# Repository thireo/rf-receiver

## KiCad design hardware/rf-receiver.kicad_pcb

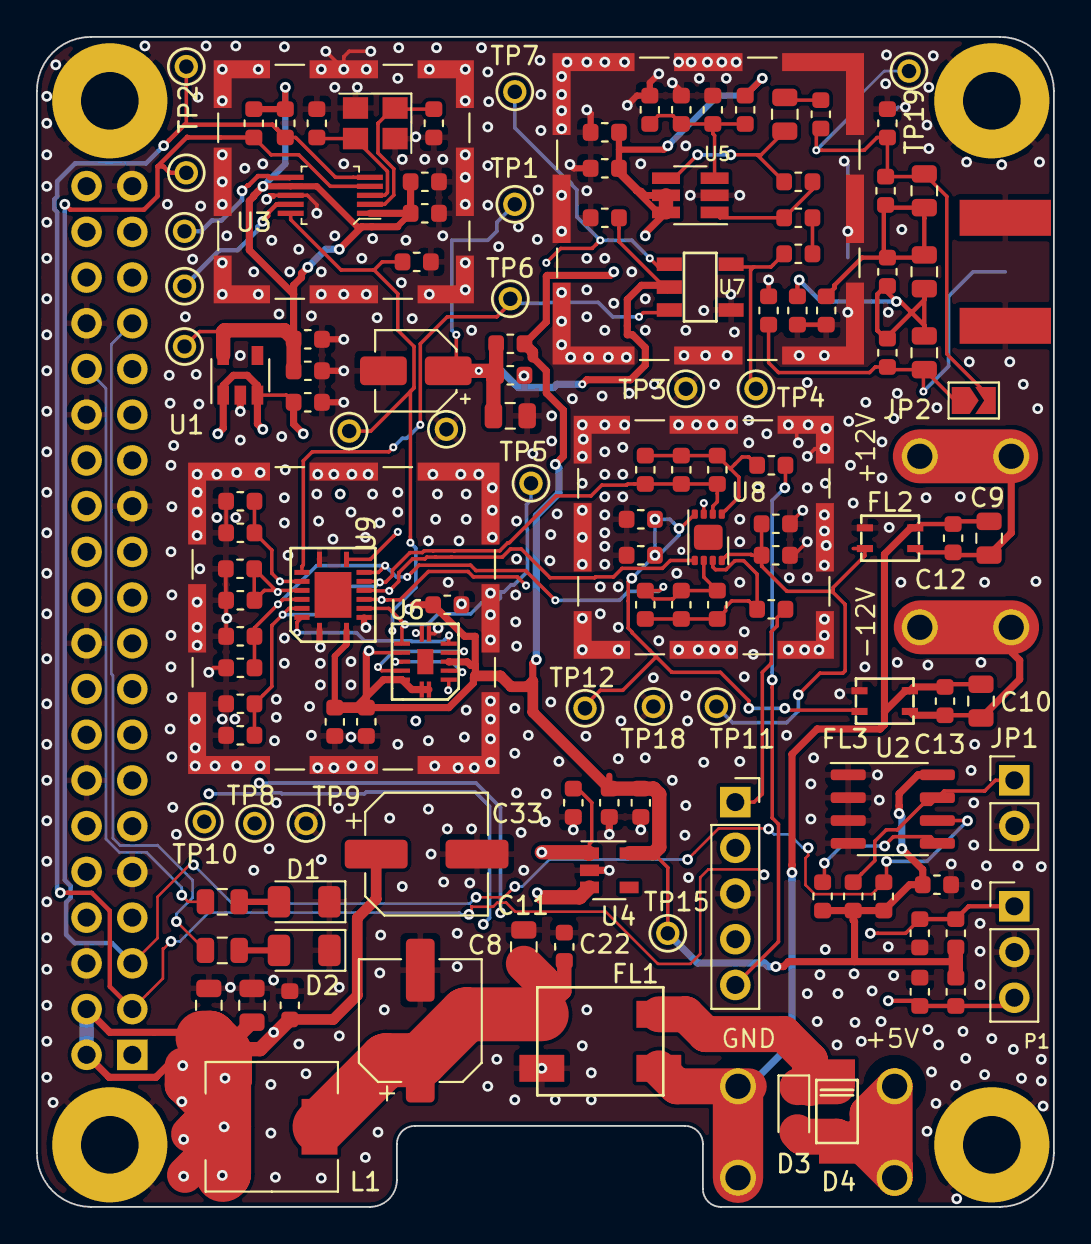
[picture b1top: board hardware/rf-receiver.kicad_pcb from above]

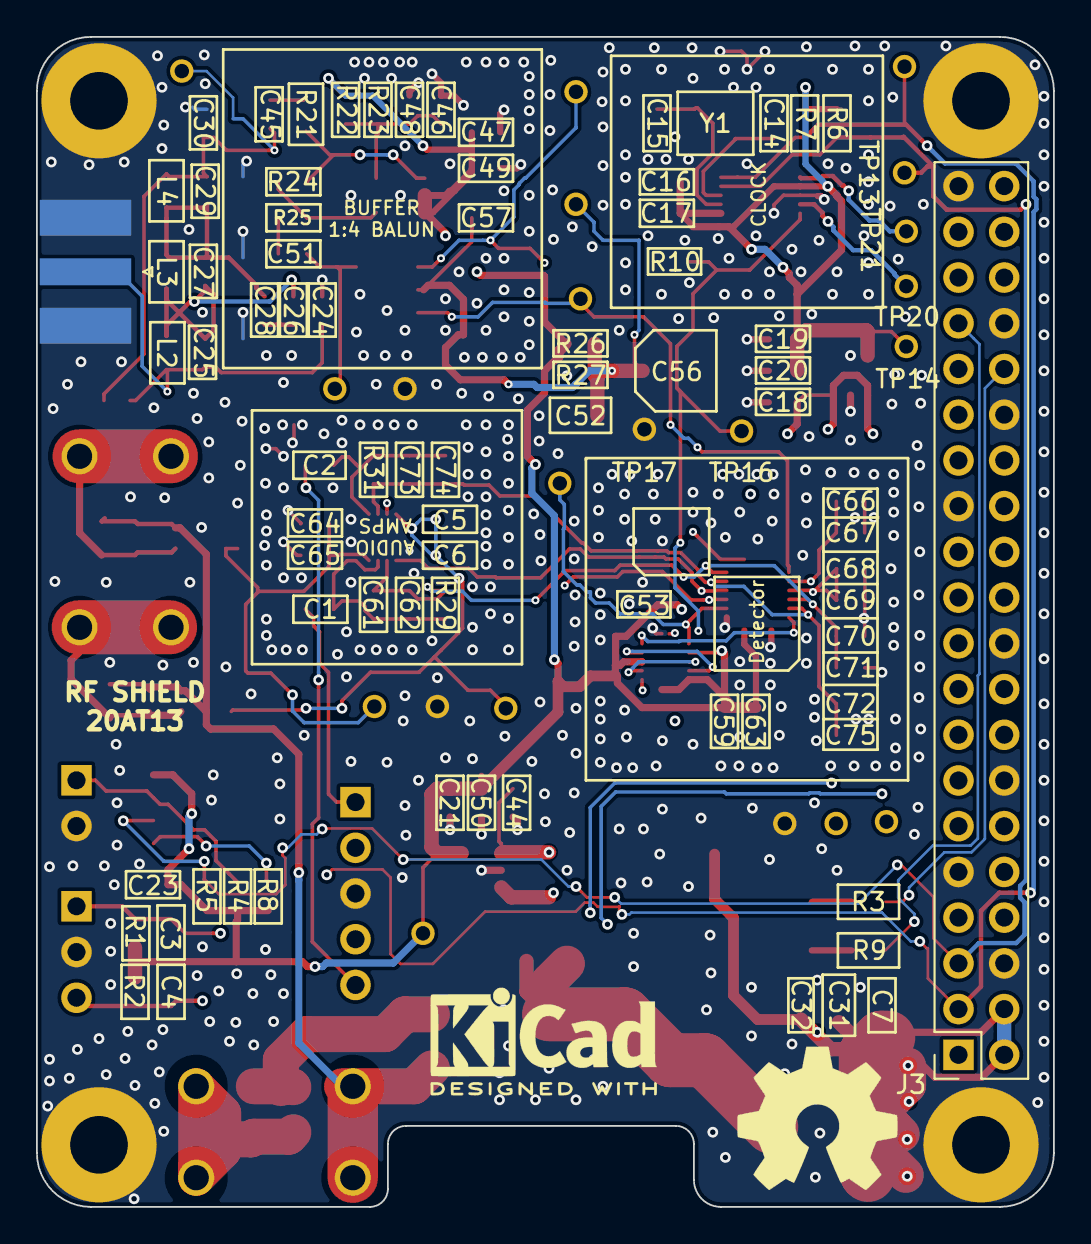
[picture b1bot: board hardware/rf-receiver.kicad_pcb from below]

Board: 4 copper layers, 56.5 x 65.0 mm, 140 parts (2 on the bottom side), 51 nets.

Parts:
C1, C2: DC BLOCK; C_0603_1608Metric
C3, C4, C12, C13, C16, C17, C20, C21, C22, C23, C32, C47, C48, C53, C63: 100nF; C_0603_1608Metric
C5, C18, C19, C44, C46, C49, C50, C64: 10uF; C_0603_1608Metric
C6, C45, C51, C57, C59, C65: 10nF; C_0603_1608Metric
C7, C9, C10, C11, C31, C52: 22uF; C_0805_2012Metric
C8, C33: 47uF/100uF; CP_Elec_6.3x5.4
C14, C15: 39pF; C_0603_1608Metric
C24, C26: 330p; C_0603_1608Metric
C25: 39p; C_0603_1608Metric
C27: 220p; C_0603_1608Metric
C28, C30: 270p; C_0603_1608Metric
C29: 130p; C_0603_1608Metric
C56: 10uF; CP_Elec_4x5.4
C61, C62, C73, C74: 0.8nF; C_0603_1608Metric
C66, C67, C68, C69, C70, C71, C72, C75: 40nF; C_0603_1608Metric
D1, D2: LED; D_1206_3216Metric
D3: D_Small_ALT; D_SOD-323_HandSoldering
D4: D_Small_ALT; SOD128
FL1: ACM90V-701-2PL-TL00; ACM70V-701-2PL-TL00
FL2, FL3: ACP3225
J1: InputConP6; PinSocket_1x05_P2.54mm_Vertical
J2: ANT; SMA_Edge-mount
J3: Raspberry_Pi_2_3; PinSocket_2x20_P2.54mm_Vertical
J4: 5_VIN; FASTON63951-1
J5, J7: RF_Shield_One_Piece; Laird_Technologies_BMI-S-102_16.50x16.50mm
J6, J8: RF_Shield_One_Piece; Laird_Technologies_BMI-S-101_13.66x12.70mm
J9: GND_IN; FASTON63951-1
J10: 12P_VIN; FASTON63951-1
J12: 12N_VIN; FASTON63951-1
JP1: Jumper_2_Open; PinHeader_1x02_P2.54mm_Vertical
JP2: SolderJumper_2_Open; SolderJumper-2_P1.3mm_Open_TrianglePad1.0x1.5mm
L1: 47+uH; L_Wuerth_HCM-7050
L2: 180n; L_0805_2012Metric
L3: 100n; L_0805_2012Metric
L4: 120n; L_0805_2012Metric
MH1, MH2, MH3, MH4: MountingHole_Pad; MountingHole_3.2mm_M3_Pad
P1: ROT_ENC; PinHeader_1x03_P2.54mm_Vertical
R1, R2, R22, R23, R29, R31: 10kohm; R_0603_1608Metric
R3, R9: 100; R_0805_2012Metric
R4: 1k; R_0603_1608Metric
R5, R8: 3k9; R_0603_1608Metric
R6, R7: I2CPULLUP; R_0603_1608Metric
R10, R25: 50ohm; R_0603_1608Metric
R21: 50ohm; R_0805_2012Metric
R24: 2.7kohm; R_0603_1608Metric
R26, R27: 2k ohm; R_0603_1608Metric
TP1: RF_DC_BIAS; testpoint_probe
TP2: SDA; testpoint_probe
TP3, TP9, TP18: GND; testpoint_probe
TP4: RF_BUFFERED; testpoint_probe
TP5: LO_A; testpoint_probe
TP6: RF_B; testpoint_probe
TP7: RF_A; testpoint_probe
TP8: LO_B; testpoint_probe
TP10: 5V_TP; testpoint_probe
TP11: 12V_TP; testpoint_probe
TP12: -12V_TP; testpoint_probe
TP13: SCL; testpoint_probe
TP14: 3.3VA; testpoint_probe
TP15: 3.3V; testpoint_probe
TP16, TP17, TP20, TP21: TestPoint; testpoint_probe
TP19: RF_POST_LP; testpoint_probe
U1, U4: MIC5504-3.3YM5; SOT-23-5
U2: CAT24C128; SOIC-8_3.9x4.9mm_P1.27mm
U3: SI5351A-B-GT; MSOP-10_W3mm
U5: OPA300; SOT-23-6_Handsoldering
U6: 74LVC74ABQ
U7: Transformer; SM-22
U8: OPA167B-DRG; SON-8-1EP_3x2mm_P0.5mm_EP1.4x1.6mm
U9: 74CBTLV3253; PVQFN16
Y1: 25MHz 20pF; Crystal_SMD_3225-4Pin_3.2x2.5mm

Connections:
+3.3VA: C16.1, C17.2, C19.1, C20.1, R6.1, R7.1, TP14.1, U1.5, U3.1, U3.7
+3V3: C21.1, C23.2, C47.2, C49.2, C50.1, C53.1, C59.1, C63.1, R1.2, R2.1, R4.1, R5.1, R8.1, R22.2, R26.2, TP15.1, U2.8, U4.5, U5.5, U5.6, U6.1, U6.4, U6.10, U6.13, U6.14, U9.16
+5V: C7.1, C18.1, C31.1, C32.2, C33.1, C44.1, J3.2, J3.4, L1.2, TP10.1, U1.1, U1.3, U4.1, U4.3
+12V: C64.2, C65.2, FL2.4, TP11.1, U8.8
-12V: C5.2, C6.2, FL3.4, TP12.1, U8.4
/I_OUT: C1.1, C61.1, C62.1, R29.1, U8.7
/Q_OUT: C2.1, C73.1, C74.1, R31.1, U8.1
/ROT_A: C3.1, J3.15, P1.1, R1.1
/ROT_B: C4.1, J3.16, P1.3, R2.2
/SCL: J3.5, R5.2, R6.2, TP13.1, U2.6, U3.4
/SDA: J3.3, R7.2, R8.2, TP2.1, U2.5, U3.5
/Tayoe Mixer sheet/0_deg: C66.1, C67.1, U8.5, U9.6, U9.12
/Tayoe Mixer sheet/30 MHz Low Pass Filter/IN: C24.1, C25.2, J2.1, JP2.1, L2.1
/Tayoe Mixer sheet/90_deg: C68.1, C69.1, U8.3, U9.5, U9.13
/Tayoe Mixer sheet/180_deg: C61.2, C62.2, C70.1, C71.1, R29.2, U8.6, U9.4, U9.10
/Tayoe Mixer sheet/270_deg: C72.1, C73.2, C74.2, C75.1, R31.2, U8.2, U9.3, U9.11
/Tayoe Mixer sheet/DC_BIAS: C52.1, C56.1, C57.1, R26.1, R27.1, TP1.1, U7.2
/Tayoe Mixer sheet/LO_IN: R10.1, TP16.1, U3.10, U6.3, U6.11
/Tayoe Mixer sheet/LO_IN_A: TP8.1, U6.6, U9.2
/Tayoe Mixer sheet/LO_IN_B: TP5.1, U6.9, U9.14
/Tayoe Mixer sheet/RF_A: TP7.1, U7.3, U9.9
/Tayoe Mixer sheet/RF_B: TP6.1, U7.1, U9.7
/Tayoe Mixer sheet/RF_BUFFERED: C51.2, TP4.1, U7.4
/Tayoe Mixer sheet/RF_IN_A: C29.1, C30.1, C45.1, JP2.2, L4.2, TP19.1
/left: C2.2, J1.5
/right: C1.2, J1.1
GND: C3.2, C4.2, C5.1, C6.1, C7.2, C8.2, C11.2, C14.1, C15.1, C16.2, C17.1, C18.2, C19.2, C20.2, C21.2, C22.2, C23.1, C24.2, C26.2, C28.2, C30.2, C31.2, C32.1, C33.2, C44.2, C46.1, C47.1, C48.1, C49.1, C50.2, C52.2, C53.2, C56.2, C57.2, C59.2, C63.2, C64.1, C65.1, C66.2, C67.2, C68.2, C69.2, C70.2, C71.2, C72.2, C75.2, D1.1, D2.1, FL1.4, FL2.3, FL3.3, J1.3, J2.2, J3.6, J3.9, J3.14, J3.20, J3.25, J3.30, J3.34, J3.39, J5.1, J6.1, J7.1, J8.1, JP1.2, MH1.1, MH2.1, MH3.1, MH4.1, P1.2, R10.2, R23.1, R27.2, TP3.1, TP9.1, TP17.1, TP18.1, U1.2, U2.1, U2.2, U2.3, U2.4, U3.8, U4.2, U5.2, U6.7, U7.5, U9.1, U9.8, U9.15, Y1.2, Y1.4
unnamed: C10.1, C13.1, FL3.1, J12.1
unnamed: C9.2, C10.2, C12.2, C13.2, FL1.1, FL2.2, FL3.2, J9.1
unnamed: C8.1, C11.1, C22.1, FL1.3, L1.1
unnamed: C9.1, C12.1, FL2.1, J10.1
unnamed: C14.2, U3.3, Y1.3
unnamed: C15.2, U3.2, Y1.1
unnamed: C25.1, C26.1, C27.2, L2.2, L3.1
unnamed: C27.1, C28.1, C29.2, L3.2, L4.1
unnamed: C45.2, R21.1
unnamed: C46.2, C48.2, R22.1, R23.2, U5.3
unnamed: C51.1, R25.2
unnamed: D1.2, R3.2
unnamed: D2.2, R9.2
unnamed: D3.1, D4.1, FL1.2
unnamed: D3.2, D4.2, J4.1
unnamed: J3.32, R3.1
unnamed: J3.33, R9.1
unnamed: JP1.1, R4.2, U2.7
unnamed: R21.2, R24.1, U5.4
unnamed: R24.2, R25.1, U5.1
unnamed: TP20.1, U3.9
unnamed: TP21.1, U3.6
unnamed: U6.2, U6.8
unnamed: U6.5, U6.12

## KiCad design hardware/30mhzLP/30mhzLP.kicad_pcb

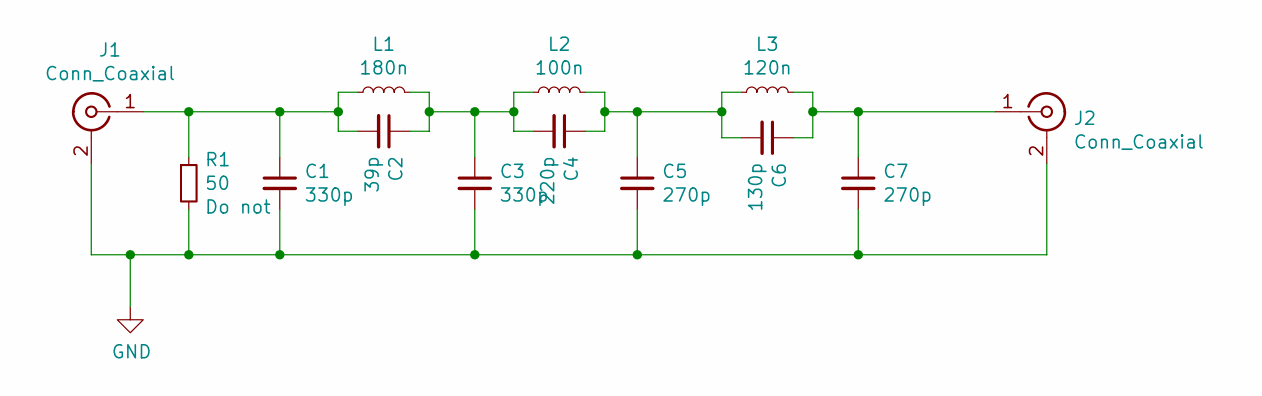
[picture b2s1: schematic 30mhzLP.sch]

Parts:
C1, C3: 330p; C_0603_1608Metric
C2: 39p; C_0603_1608Metric
C4: 220p; C_0603_1608Metric
C5, C7: 270p; C_0603_1608Metric
C6: 130p; C_0603_1608Metric
J1, J2: Conn_Coaxial; SMA_Amphenol_132289_EdgeMount
L1: 180n; L_0805_2012Metric
L2: 100n; L_0805_2012Metric
L3: 120n; L_0805_2012Metric
R1: 50; R_0805_2012Metric

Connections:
GND: C1.2, C3.2, C5.2, C7.2, J1.2 (Ext), J2.2 (Ext), R1.2
unnamed: C1.1, C2.2, J1.1 (In), L1.1, R1.1
unnamed: C2.1, C3.1, C4.2, L1.2, L2.1
unnamed: C4.1, C5.1, C6.2, L2.2, L3.1
unnamed: C6.1, C7.1, J2.1 (In), L3.2

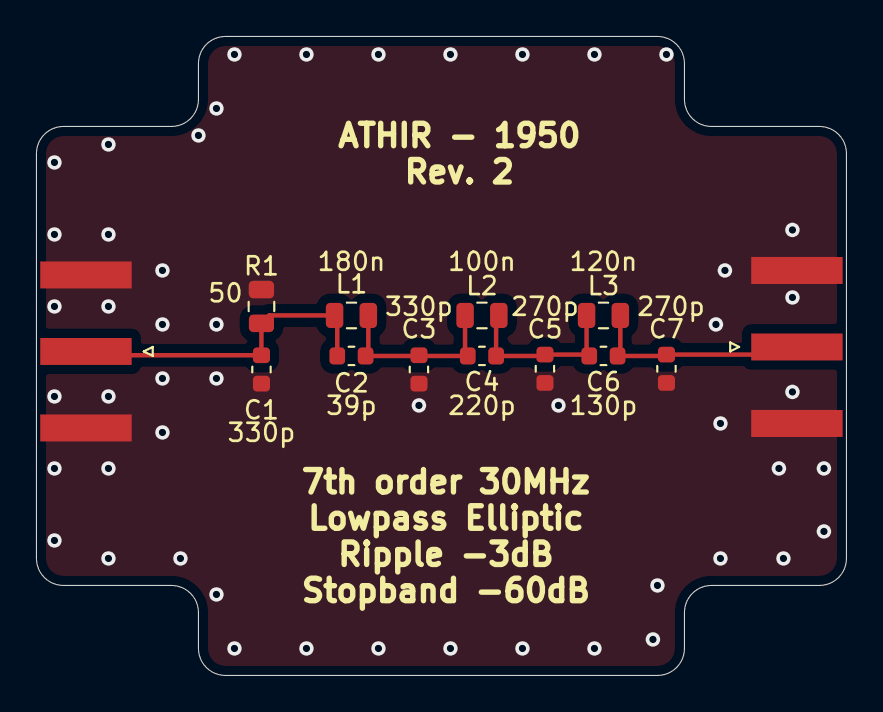
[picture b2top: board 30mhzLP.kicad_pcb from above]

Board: 2 copper layers, 45.0 x 35.5 mm, 13 parts (0 on the bottom side), 5 nets.

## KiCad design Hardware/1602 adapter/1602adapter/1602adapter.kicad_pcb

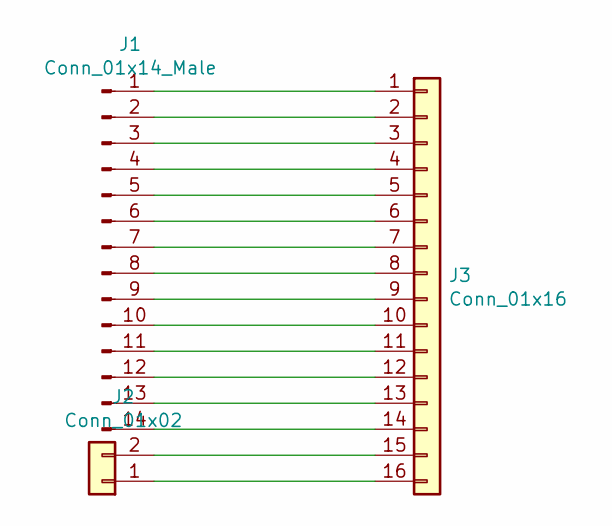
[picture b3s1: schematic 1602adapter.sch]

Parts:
J1: Conn_01x14_Male; PinHeader_1x14_P2.54mm_Vertical
J2: Conn_01x02; JST_XH_B2B-XH-A_1x02_P2.50mm_Vertical
J3: Conn_01x16; PinHeader_1x16_P2.54mm_Vertical

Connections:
unnamed: J1.1, J3.1
unnamed: J1.2, J3.2
unnamed: J1.3, J3.3
unnamed: J1.4, J3.4
unnamed: J1.5, J3.5
unnamed: J1.6, J3.6
unnamed: J1.7, J3.7
unnamed: J1.8, J3.8
unnamed: J1.9, J3.9
unnamed: J1.10, J3.10
unnamed: J1.11, J3.11
unnamed: J1.12, J3.12
unnamed: J1.13, J3.13
unnamed: J1.14, J3.14
unnamed: J2.1, J3.16
unnamed: J2.2, J3.15

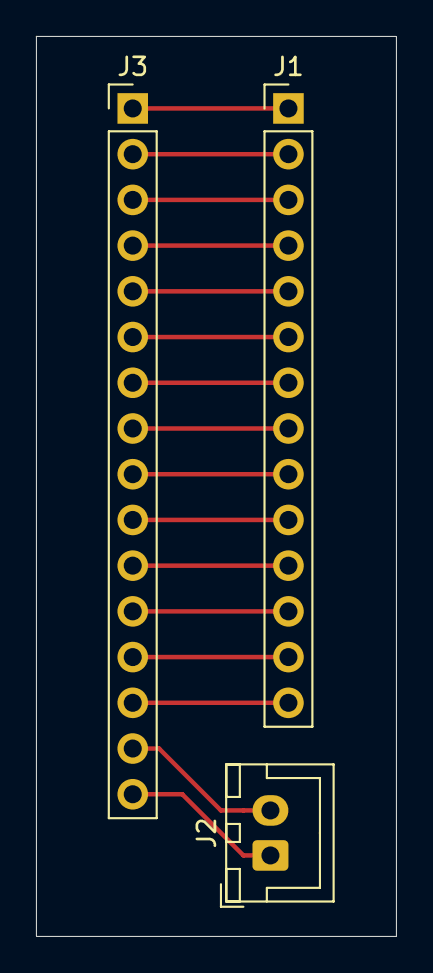
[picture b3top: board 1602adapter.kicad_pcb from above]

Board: 2 copper layers, 20.0 x 50.0 mm, 3 parts (0 on the bottom side), 16 nets.

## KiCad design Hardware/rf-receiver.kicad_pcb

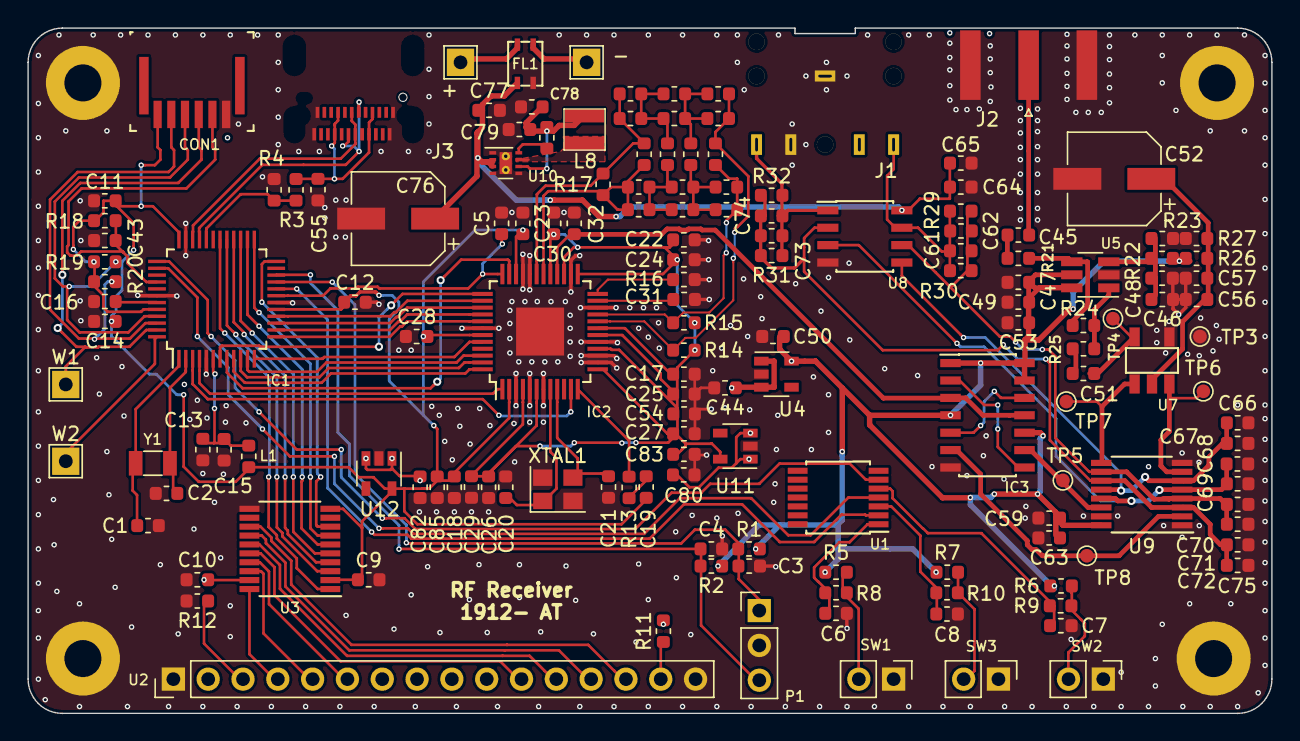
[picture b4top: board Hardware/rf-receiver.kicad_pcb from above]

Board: 4 copper layers, 90.8 x 50.0 mm, 160 parts (0 on the bottom side), 98 nets.

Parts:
+: PSU+; TestPoint_THTPad_2.0x2.0mm_Drill1.0mm
-: PSU-; TestPoint_THTPad_2.0x2.0mm_Drill1.0mm
C1, C2: 15pF; C_0603_1608Metric
C3, C4, C5, C6, C7, C8, C12, C14, C15, C16, C17, C18, C22, C23, C24, C25, C26, C27, C28, C29, C30, C43, C44, C47, C48, C54, C77, C79, C80, C82: 100nF; C_0603_1608Metric
C9, C10, C53, C63: 0.1uF; C_0603_1608Metric
C11, C13, C46, C49, C50, C56, C64, C83, C85: 10uF; C_0603_1608Metric
C19, C45, C51, C57, C59, C65: 10nF; C_0603_1608Metric
C20, C21, C34, C35, C39: 39pF; C_0603_1608Metric
C31: 1uF; C_0603_1608Metric
C32, C33, C37, C38: 22pF; C_0603_1608Metric
C36, C42: 33pF; C_0603_1608Metric
C40, C41: 7.5pF; C_0603_1608Metric
C52: 47uF; CP_Elec_6.3x7.7
C55: C_Small; C_0603_1608Metric
C61, C62, C73, C74: 0.8nF; C_0603_1608Metric
C66, C67, C68, C69, C70, C71, C72, C75: 40nF; C_0603_1608Metric
C76: 100uF; CP_Elec_6.3x7.7
C78: 22uF; C_0603_1608Metric
CON1: FPC_6POS; HFW6R_2STE1LF
FL1: ACP3225
IC1: ATSAMD21G18A-AU; TQFP-48_7x7mm_P0.5mm
IC2: AD9954; TQFP-48-1EP_7x7mm_P0.5mm_EP3.5x3.5mm
IC3: 74LVC74; SOIC-14_3.9x8.7mm_P1.27mm
J1: Conn_01x05_Female; SJ1-35235
J2: Conn_Coaxial; SMA_Amphenol_132289_EdgeMount
J3: USB_C_Receptacle; DX07S024JJ
L1: SMD-FERRITE-CHIP-120-OHM-500MA_0603_; C_0603_1608Metric
L2, L3: 12nH; L_0603_1608Metric
L4, L5: 18nH; L_0603_1608Metric
L6, L7: 20nH; L_0603_1608Metric
L8: 2.2uH; XFL3012
MH1, MH2, MH3, MH4: MountingHole_Pad; MountingHole_2.7mm_M2.5_Pad
P1: ROT_ENC; PinHeader_1x03_P2.54mm_Vertical
R1, R2, R5, R6, R7, R8, R9, R10, R22, R23, R29, R30, R31, R32: 10kohm; R_0603_1608Metric
R3, R4: R_Small; R_0603_1608Metric
R11: 220ohm; R_0603_1608Metric
R12: 2kohm; R_0603_1608Metric
R13: 243ohm; R_0603_1608Metric
R14, R15, R17, R21, R25: 50ohm; R_0603_1608Metric
R16: 3.92kohm; R_0603_1608Metric
R18, R19, R20: 100kohm; R_0603_1608Metric
R24: 2.7kohm; R_0603_1608Metric
R26, R27: 2k ohm; R_0603_1608Metric
R33: 100k; R_0603_1608Metric
SW1: BTN1; PinHeader_1x02_P2.54mm_Vertical
SW2: BTN2; PinHeader_1x02_P2.54mm_Vertical
SW3: BTN3; PinHeader_1x02_P2.54mm_Vertical
TP3: GND; TestPoint_Pad_D1.0mm
TP4: RF_BUFFERED; TestPoint_Pad_D1.0mm
TP5: LO_A; TestPoint_Pad_D1.0mm
TP6: RF_B; TestPoint_Pad_D1.0mm
TP7: RF_A; TestPoint_Pad_D1.0mm
TP8: LO_B; TestPoint_Pad_D1.0mm
U1: 74HC14; TSSOP-14_4.4x5mm_P0.65mm
U2: RC1602A; PinHeader_1x16_P2.54mm_Vertical
U3: TXB0108PWR; TSSOP-20_4.4x6.5mm_P0.65mm
U4: MIC5504-3.3YM5; SOT-23-5
U5: OPA300; SOT-23-6_Handsoldering
U7: Transformer; SM-22
U8: NE5532; SOIC-8_3.9x4.9mm_P1.27mm
U9: 74CBTLV3253; TSSOP-16_4.4x5mm_P0.65mm
U10: TPS62173DSG; WSON-8-1EP_2x2mm_P0.5mm_EP0.9x1.6mm_ThermalVias
U11, U12: MIC5504-1.8YM5; SOT-23-5
W1: TX; TestPoint_THTPad_2.0x2.0mm_Drill1.0mm
W2: RX; TestPoint_THTPad_2.0x2.0mm_Drill1.0mm
XTAL1: 25MHz 20pF; Crystal_SMD_3225-4Pin_3.2x2.5mm
Y1: Crystal_Small; Crystal_SMD_3215-2Pin_3.2x1.5mm

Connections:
+1V8: C9.1, C11.1, C12.1, C14.1, C18.2, C19.2, C23.2, C28.2, C85.1, CON1.1, IC1.17, IC1.36, IC1.44, IC2.2, IC2.34, IC2.43, L1.1, R18.1, R19.1, R20.1, U3.2, U3.10, U12.5
+3V3: C47.2, C49.2, C50.1, C53.1, C59.1, C63.1, IC3.1, IC3.4, IC3.10, IC3.13, IC3.14, R1.2, R2.1, R5.1, R6.1, R7.1, R22.2, R26.2, U4.5, U5.5, U5.6, U9.16
+5V: C10.1, C44.1, C78.1, C79.1, C80.1, C82.1, L8.2, R11.2, R33.2, U2.2, U3.19, U4.1, U4.3, U10.6, U11.1, U11.3, U12.1, U12.3
+12V: C64.2, C65.2, C76.1, C77.1, FL1.1, U8.8, U10.2, U10.3
/AD9954sheet/COMP_OUT: C32.1, IC2.28, IC3.3, IC3.11
/AD9954sheet/IOUT+: C41.2, C42.2, IC2.21, L7.1, R15.1
/AD9954sheet/IOUT-: C40.2, C42.1, IC2.20, L6.2, R14.1
/BTN1: IC1.20, U1.2
/BTN2: IC1.37, U1.6
/BTN3: IC1.38, U1.4
/CLKMODESEL: IC1.3, IC2.11
/DDS_RESET: C5.1, IC1.19, IC2.36
/IOSYNC: IC1.7, IC2.37
/IOUPDATE: IC1.4, IC2.1
/JTAGConn58895F8D/MCU_RESET: C43.1, CON1.5, IC1.40, R18.2
/JTAGConn58895F8D/SWCLK: CON1.3, IC1.45, R19.2
/JTAGConn58895F8D/SWDIO: CON1.2, IC1.46, R20.2
/LCD_D4: IC1.27, U3.5
/LCD_D5: IC1.26, U3.6
/LCD_D6: IC1.25, U3.7
/LCD_D7: IC1.24, U3.8
/LCD_EN: IC1.28, U3.4
/LCD_RS: IC1.30, U3.1
/LCD_RW: IC1.29, U3.3
/OSK: IC1.11, IC2.46
/PS0: IC1.10, IC2.47
/PS1: IC1.9, IC2.48
/PWRDWNCTL: IC1.8, IC2.35
/ROT_A: C3.1, IC1.21, P1.1, R1.1
/ROT_B: C4.1, IC1.22, P1.3, R2.2
/SCLK: IC1.14, IC2.40
/SDIO: IC1.13, IC2.41
/SDO: IC1.16, IC2.38
/SYNC_IN: IC1.12, IC2.44
/Tayoe Mixer sheet/0_deg: C66.1, C67.1, U8.5, U9.6, U9.12
/Tayoe Mixer sheet/90_deg: C68.1, C69.1, U8.3, U9.5, U9.13
/Tayoe Mixer sheet/180_deg: C61.2, C62.2, C70.1, C71.1, R29.2, R30.2, U8.6, U9.4, U9.10
/Tayoe Mixer sheet/270_deg: C72.1, C73.2, C74.2, C75.1, R31.2, R32.2, U8.2, U9.3, U9.11
/Tayoe Mixer sheet/DC_BIAS: C52.1, C56.1, C57.1, R26.1, R27.1, U7.2
/Tayoe Mixer sheet/I_OUT: C61.1, C62.1, J1.3, R29.1, R30.1, U8.7
/Tayoe Mixer sheet/LO_IN_A: IC3.6, TP8.1, U9.2
/Tayoe Mixer sheet/LO_IN_B: IC3.9, TP5.1, U9.14
/Tayoe Mixer sheet/Q_OUT: C73.1, C74.1, J1.2, R31.1, R32.1, U8.1
/Tayoe Mixer sheet/RF_A: TP7.1, U7.3, U9.9
/Tayoe Mixer sheet/RF_B: TP6.1, U7.1, U9.7
/Tayoe Mixer sheet/RF_BUFFERED: C51.2, TP4.1, U7.4
/Tayoe Mixer sheet/RF_IN_A: C45.1, J2.1
/UART_RX: IC1.48, W2.1
/UART_TX: CON1.4, IC1.47, W1.1
/USB_D+: IC1.34, J3.A6, J3.B6
/USB_D-: IC1.33, J3.A7, J3.B7
/USB_VCC: IC1.32, R3.1, R4.1
/VDDANA: C13.1, C15.1, IC1.6, L1.2
/VDDCORE: C16.1, IC1.43
/~CS: IC1.15, IC2.39
GND: C1.2, C2.2, C3.2, C4.2, C5.2, C6.2, C7.2, C8.2, C9.2, C10.2, C11.2, C12.2, C13.2, C14.2, C15.2, C16.2, C17.1, C18.1, C20.1, C21.2, C22.1, C23.1, C24.1, C25.1, C26.1, C27.1, C28.1, C29.1, C30.1, C31.2, C32.2, C43.2, C44.2, C46.1, C47.1, C48.1, C49.1, C50.2, C52.2, C53.2, C54.1, C55.2, C56.2, C57.2, C59.2, C63.2, C64.1, C65.1, C66.2, C67.2, C68.2, C69.2, C70.2, C71.2, C72.2, C75.2, C76.2, C77.2, C78.2, C79.2, C80.2, C82.2, C83.2, C85.2, CON1.6, FL1.2, IC1.5, IC1.18, IC1.35, IC1.42, IC2.3, IC2.5, IC2.7, IC2.14, IC2.15, IC2.17, IC2.22, IC2.26, IC2.32, IC2.33, IC2.42, IC2.49, IC3.7, J1.1, J1.4, J2.2, J3.A1, J3.A12, J3.B1, J3.B12, MH1.1, MH2.1, MH3.1, MH4.1, P1.2, R4.2, R12.2, R16.1, R23.1, R27.2, SW1.1, SW2.1, SW3.1, TP3.1, U2.1, U2.16, U3.11, U4.2, U5.2, U7.5, U8.4, U9.1, U9.8, U9.15, U10.1, U10.4, U10.5, U10.9, U11.2, U12.2, XTAL1.2, XTAL1.4
unnamed: C1.1, IC1.1, Y1.1
unnamed: C2.1, IC1.2, Y1.2
unnamed: C6.1, R8.2, U1.1
unnamed: C7.1, R9.2, U1.5
unnamed: C8.1, R10.2, U1.3
unnamed: C19.1, R13.2
unnamed: C20.2, IC2.8, XTAL1.1
unnamed: C21.1, IC2.9, XTAL1.3
unnamed: C31.1, IC2.23
unnamed: C33.1, C34.1, IC2.31, L2.1, R17.1
unnamed: C33.2, C35.1, IC2.30, L3.2, R17.2
unnamed: C34.2, C36.1, C37.1, L2.2, L4.1
unnamed: C35.2, C36.2, C38.1, L3.1, L5.2
unnamed: C37.2, C39.1, C40.1, L4.2, L6.1
unnamed: C38.2, C39.2, C41.1, L5.1, L7.2
unnamed: C45.2, R21.1
unnamed: C46.2, C48.2, R22.1, R23.2, U5.3
unnamed: C51.1, R25.2
unnamed: C55.1, J3.A4, J3.A9, J3.B4, J3.B9, R3.2
unnamed: -.1, FL1.3
unnamed: +.1, FL1.4
unnamed: IC2.12, R13.1
unnamed: IC2.24, R16.2
unnamed: IC3.2, IC3.8
unnamed: IC3.5, IC3.12
unnamed: L8.1, U10.7
unnamed: R5.2, R8.1, SW1.2
unnamed: R6.2, R9.1, SW2.2
unnamed: R7.2, R10.1, SW3.2
unnamed: R11.1, U2.15
unnamed: R12.1, U2.3
unnamed: R21.2, R24.1, U5.4
unnamed: R24.2, R25.1, U5.1
unnamed: R33.1, U10.8
unnamed: U2.4, U3.20
unnamed: U2.5, U3.18
unnamed: U2.6, U3.17
unnamed: U2.11, U3.16
unnamed: U2.12, U3.15
unnamed: U2.13, U3.14
unnamed: U2.14, U3.13
VAA: C17.2, C22.2, C24.2, C25.2, C26.2, C27.2, C29.2, C30.2, C54.2, C83.1, IC2.4, IC2.6, IC2.13, IC2.16, IC2.18, IC2.19, IC2.25, IC2.27, IC2.29, R14.2, R15.2, U11.5

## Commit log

2017-01-17 First initial Commit
2019-01-20 First actual HW commit
    Updated to KiCAD 5.0
2019-01-22 Second actual HW commit
    First finished draft of HW layout and PCB design.
2019-01-23 Added more GND vias
2019-01-23 Moved IQ out to the back
2019-01-24 Added BOM
    Added BOM.csv
    Added Micro-USB
2019-01-25 HW PCB changes
    Added IBOM
    Added extra spacing between 0402 components.
2019-01-25 Fixed Silkscreen
2019-01-25 Added GND vias
2019-01-26 HW: Fixed mini-jack position
    Added Gerber files.
    Moved the mini-jack back and added a cutout in the PCB.
2019-03-09 Added 3D models...
    25MHz oscillator -> footprint no longer handsoldering variant.
2019-03-22 HW rev1
2019-03-27 HW rev. 1 - Gerbers
    HW: 0406 -> 0603
2019-05-10 Added LCD datasheets
    Potential new LCDs.
2019-05-10 Added 30 MHz LP filter
2019-07-05 Started work on gnuradio side of project
    Goal: Display fft and demodulate.
2019-07-06 Added png example of ssb IQ demod.
2019-07-06 First successful SSB demodulator. Added example files as well.
2019-07-13 No more capitalcase letters in path
2019-08-11 Added first prototype of RPi DSP Gnuradio project
2019-08-13 Added example project
2019-08-18 Worked LSB, USB and CW. SSB tested on 27.4 MHz with CB radio. Might have internal LO frequency drifting. Unknown if CB or receiver.
2020-02-26 Finished work on Receiver RPi shield. Changed CLK to SI5351A. Minimized footprints for almost all Tayloe detector ICs. Added -12V to audio opamps. Prepared board for coexisting with Hifiberry.
2020-02-26 Added rpi changes - seems weird that I forgot that for so long
2020-02-26 temp
2020-02-26 HW: Fixed SMA footprint and 74x3253 footprint
2020-08-21 Sorry future me
2020-08-21 Sorry
